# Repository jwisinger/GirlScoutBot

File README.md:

# GirlScoutBot
Simple STM32 based car/robot design for Girl Scout Badges

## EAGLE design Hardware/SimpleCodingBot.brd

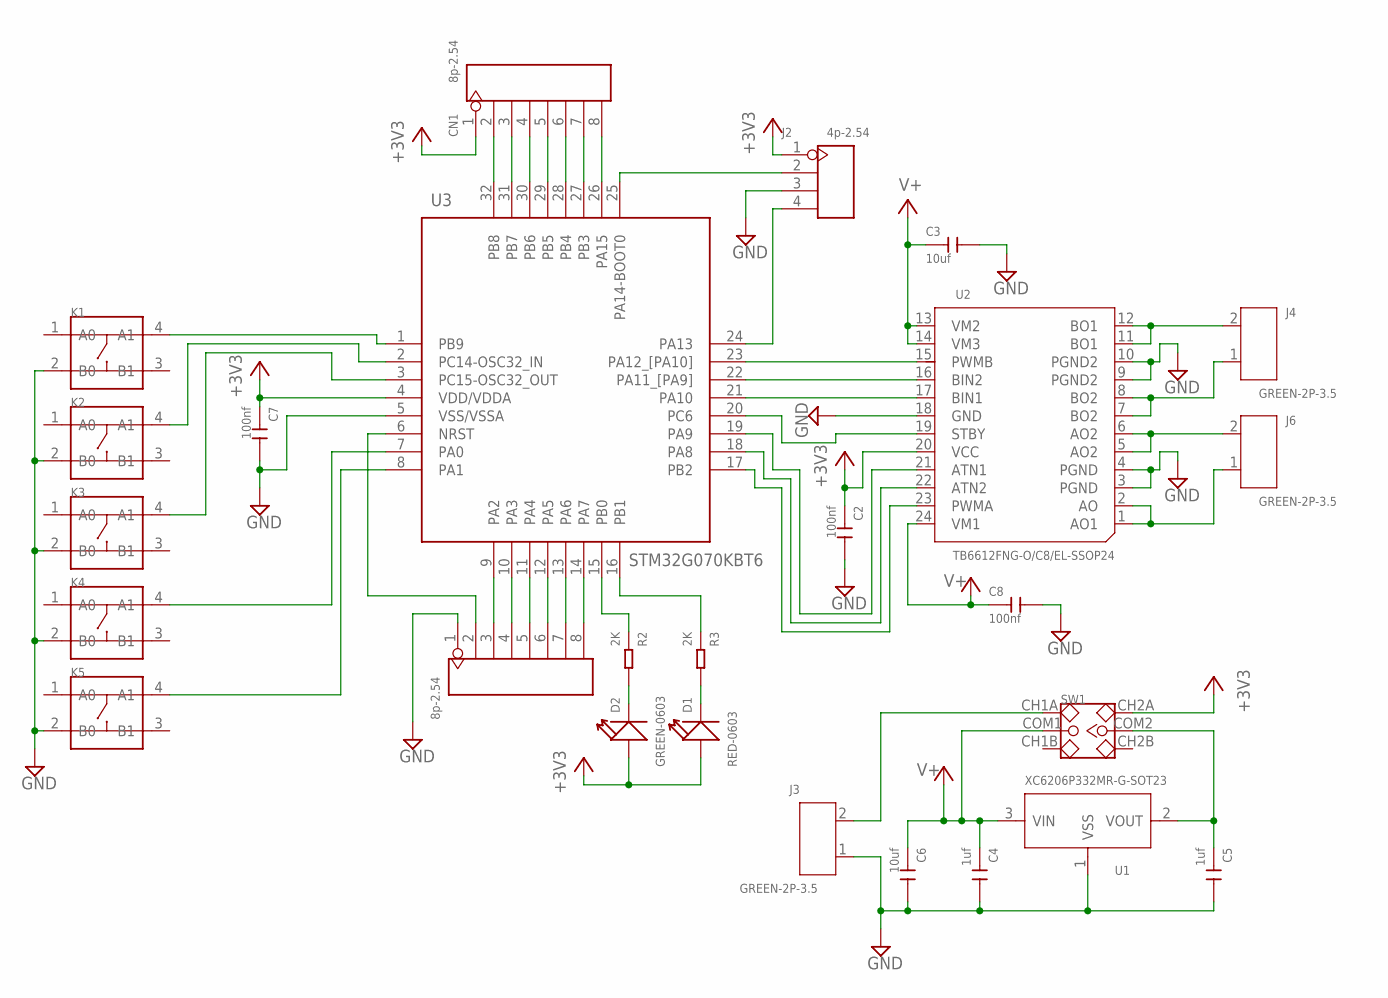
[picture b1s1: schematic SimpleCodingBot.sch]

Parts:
C2, C7, C8: 100nf; C0603
C3, C6: 10uf; C0603
C4, C5: 1uf; C0603
CN1, CN2: 8p-2.54; H8-2.54
D1: RED-0603; LED-0603
D2: GREEN-0603; LED-0603
J2: 4p-2.54; H4-2.54
J3, J4, J6: GREEN-2P-3.5; H2-3.5-7.0X7.0MM
K1, K2, K3, K4, K5: DIP-SWITCH-TACTILE-SPST-NO/TS-1109(4P-D6.0MM)'TS-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; SW4-6.0X6.0X5.0MM
R2, R3: 2K; R0603
SW1: DIP-TOGGLE-SWITCH-2CH-(2X3P-2.54); SW6-2.54-9.0X3.5X3.2+2.0MM
U1: XC6206P332MR-G-SOT23; SOT-23
U2: TB6612FNG-O/C8/EL-SSOP24; SSOP24-0.65-8.9X5.3MM
U3: STM32G070KBT6; QFP80P900X900X160-32N

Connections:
+3V3: C2.1, C7.1, CN1.1, D1.+, D2.+, J2.1, SW1.CH2A, U2.20 (VCC), U3.4 (VDD/VDDA)
GND: C2.2, C3.2, C4.2, C5.2, C6.2, C7.2, C8.2, CN2.1, J2.3, J3.1, K1.2 (B0), K2.2 (B0), K3.2 (B0), K4.2 (B0), K5.2 (B0), U1.1 (VSS), U2.3 (PGND), U2.4 (PGND), U2.9 (PGND2), U2.10 (PGND2), U2.18 (GND), U3.5 (VSS/VSSA)
unnamed: CN1.6, U3.28 (PB4)
unnamed: C5.1, SW1.COM2, U1.2 (VOUT)
unnamed: K1.4 (A1), U3.1 (PB9)
unnamed: K2.4 (A1), U3.2 (PC14-OSC32_IN)
unnamed: K3.4 (A1), U3.3 (PC15-OSC32_OUT)
unnamed: K4.4 (A1), U3.7 (PA0)
unnamed: K5.4 (A1), U3.8 (PA1)
unnamed: J2.2, U3.25 (PA14-BOOT0)
unnamed: J2.4, U3.24 (PA13)
unnamed: D1.-, R3.2
unnamed: J3.2, SW1.CH1A
unnamed: R3.1, U3.16 (PB1)
unnamed: R2.1, U3.15 (PB0)
unnamed: CN2.8, U3.14 (PA7)
unnamed: U2.15 (PWMB), U3.23 (PA12_[PA10])
unnamed: U2.16 (BIN2), U3.22 (PA11_[PA9])
unnamed: CN1.5, U3.29 (PB5)
unnamed: CN1.4, U3.30 (PB6)
unnamed: CN1.3, U3.31 (PB7)
unnamed: CN1.2, U3.32 (PB8)
unnamed: U2.17 (BIN1), U3.21 (PA10)
unnamed: CN2.7, U3.13 (PA6)
unnamed: CN2.6, U3.12 (PA5)
unnamed: CN1.7, U3.27 (PB3)
unnamed: CN2.5, U3.11 (PA4)
unnamed: U2.21 (ATN1), U3.19 (PA9)
unnamed: CN2.4, U3.10 (PA3)
unnamed: U2.22 (ATN2), U3.18 (PA8)
unnamed: U2.23 (PWMA), U3.17 (PB2)
unnamed: CN2.3, U3.9 (PA2)
unnamed: U2.19 (STBY), U3.20 (PC6)
unnamed: CN1.8, U3.26 (PA15)
unnamed: D2.-, R2.2
unnamed: CN2.2, U3.6 (NRST)
unnamed: J4.2, U2.11 (BO1), U2.12 (BO1)
unnamed: J4.1, U2.7 (BO2), U2.8 (BO2)
unnamed: J6.2, U2.5 (AO2), U2.6 (AO2)
unnamed: J6.1, U2.1 (AO1), U2.2 (AO)
V+: C3.1, C4.1, C6.1, C8.1, SW1.COM1, U1.3 (VIN), U2.13 (VM2), U2.14 (VM3), U2.24 (VM1)

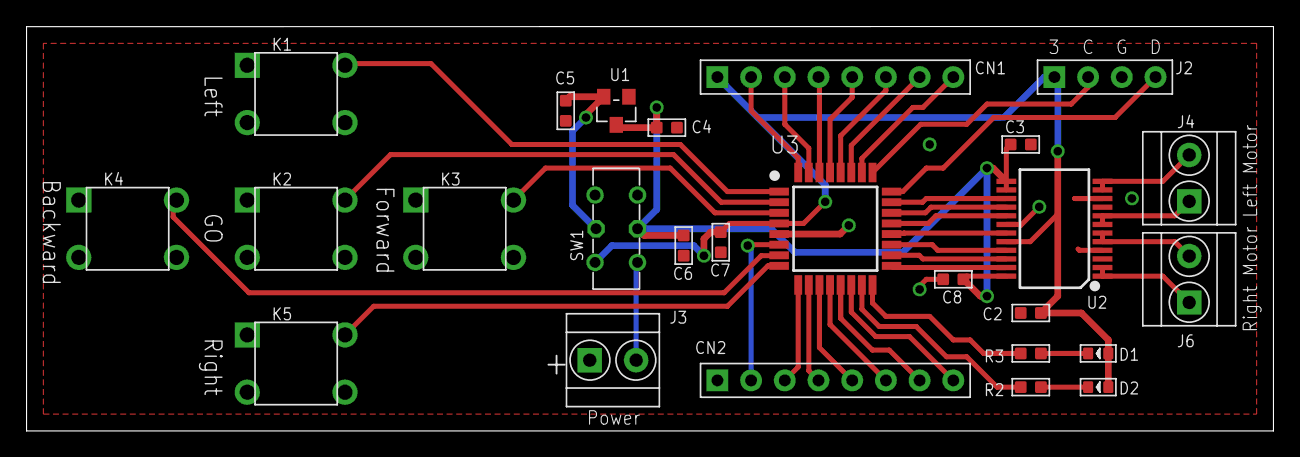
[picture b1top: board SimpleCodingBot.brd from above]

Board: 2 copper layers, 94.0 x 30.5 mm, 26 parts (0 on the bottom side), 41 nets.

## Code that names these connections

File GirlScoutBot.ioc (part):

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Mcu.Name=STM32F103C(8-B)Tx
Mcu.Package=LQFP48
Mcu.UserName=STM32F103C8Tx
PA0-WKUP.GPIOParameters=GPIO_Label
PA0-WKUP.GPIO_Label=ENTER_RTN
PA0-WKUP.Signal=GPIO_Output
PA10.GPIOParameters=GPIO_Label
PA10.GPIO_Label=RADIO_RESET
PA10.Signal=GPIO_Output
PA13.Mode=Serial_Wire
PA13.Signal=SYS_JTMS-SWDIO
PA14.Mode=Serial_Wire
PA14.Signal=SYS_JTCK-SWCLK
PA2.GPIOParameters=GPIO_PuPd,GPIO_Label,GPIO_ModeDefaultEXTI
PA2.GPIO_Label=ENTER
PA2.GPIO_ModeDefaultEXTI=GPIO_MODE_IT_FALLING
PA2.GPIO_PuPd=GPIO_PULLUP
PA2.Signal=GPXTI2
PA3.GPIOParameters=GPIO_PuPd,GPIO_Label,GPIO_ModeDefaultEXTI
PA3.GPIO_Label=UP
PA3.GPIO_ModeDefaultEXTI=GPIO_MODE_IT_FALLING
PA3.GPIO_PuPd=GPIO_PULLUP
PA3.Signal=GPXTI3
PA5.GPIOParameters=GPIO_Label
PA5.GPIO_Label=UP_RTN
PA5.Signal=GPIO_Output
PA6.GPIOParameters=GPIO_Label
PA6.GPIO_Label=RIGHT_RTN
PA6.Signal=GPIO_Output
PA8.GPIOParameters=GPIO_Label
PA8.GPIO_Label=RADIO_INT
PA8.Signal=GPXTI8
PA9.GPIOParameters=GPIO_Label
PA9.GPIO_Label=RADIO_CS
PA9.Signal=GPIO_Output
PB0.GPIOParameters=GPIO_PuPd,GPIO_Label,GPIO_ModeDefaultEXTI
PB0.GPIO_Label=RIGHT
PB0.GPIO_ModeDefaultEXTI=GPIO_MODE_IT_FALLING
PB0.GPIO_PuPd=GPIO_PULLUP
PB0.Signal=GPXTI0
PB1.GPIOParameters=GPIO_Label
PB1.GPIO_Label=LEFT_RET
PB1.Signal=GPIO_Output
PB11.GPIOParameters=GPIO_PuPd,GPIO_Label,GPIO_ModeDefaultEXTI
PB11.GPIO_Label=LEFT
PB11.GPIO_ModeDefaultEXTI=GPIO_MODE_IT_FALLING
PB11.GPIO_PuPd=GPIO_PULLUP
PB11.Signal=GPXTI11
PB13.Mode=Full_Duplex_Master
PB13.Signal=SPI2_SCK
PB14.Mode=Full_Duplex_Master
PB14.Signal=SPI2_MISO
PB15.Mode=Full_Duplex_Master
PB15.Signal=SPI2_MOSI
PB5.GPIOParameters=PinState,GPIO_Label
PB5.GPIO_Label=RIGHT_MOTOR
PB5.PinState=GPIO_PIN_RESET
PB5.Signal=GPIO_Output
PB7.GPIOParameters=PinState,GPIO_Label
PB7.GPIO_Label=LEFT_MOTOR
PB7.PinState=GPIO_PIN_RESET
PB7.Signal=GPIO_Output
PB9.GPIOParameters=GPIO_Label
PB9.GPIO_Label=DOWN
PB9.Signal=GPXTI9
PC13-TAMPER-RTC.GPIOParameters=PinState,GPIO_Label
PC13-TAMPER-RTC.GPIO_Label=LED
PC13-TAMPER-RTC.PinState=GPIO_PIN_SET
PC13-TAMPER-RTC.Signal=GPIO_Output
board=custom

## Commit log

2019-08-23 Initial Checkin
2019-08-24 Added BLE Support
2019-08-24 Synced up with Cube
2019-08-24 General cleanup
2019-08-25 Added further BLE support
2019-08-26 Improved BLE Communication
2019-08-31 Adjusted pin mappings
2019-09-01 Create fake
